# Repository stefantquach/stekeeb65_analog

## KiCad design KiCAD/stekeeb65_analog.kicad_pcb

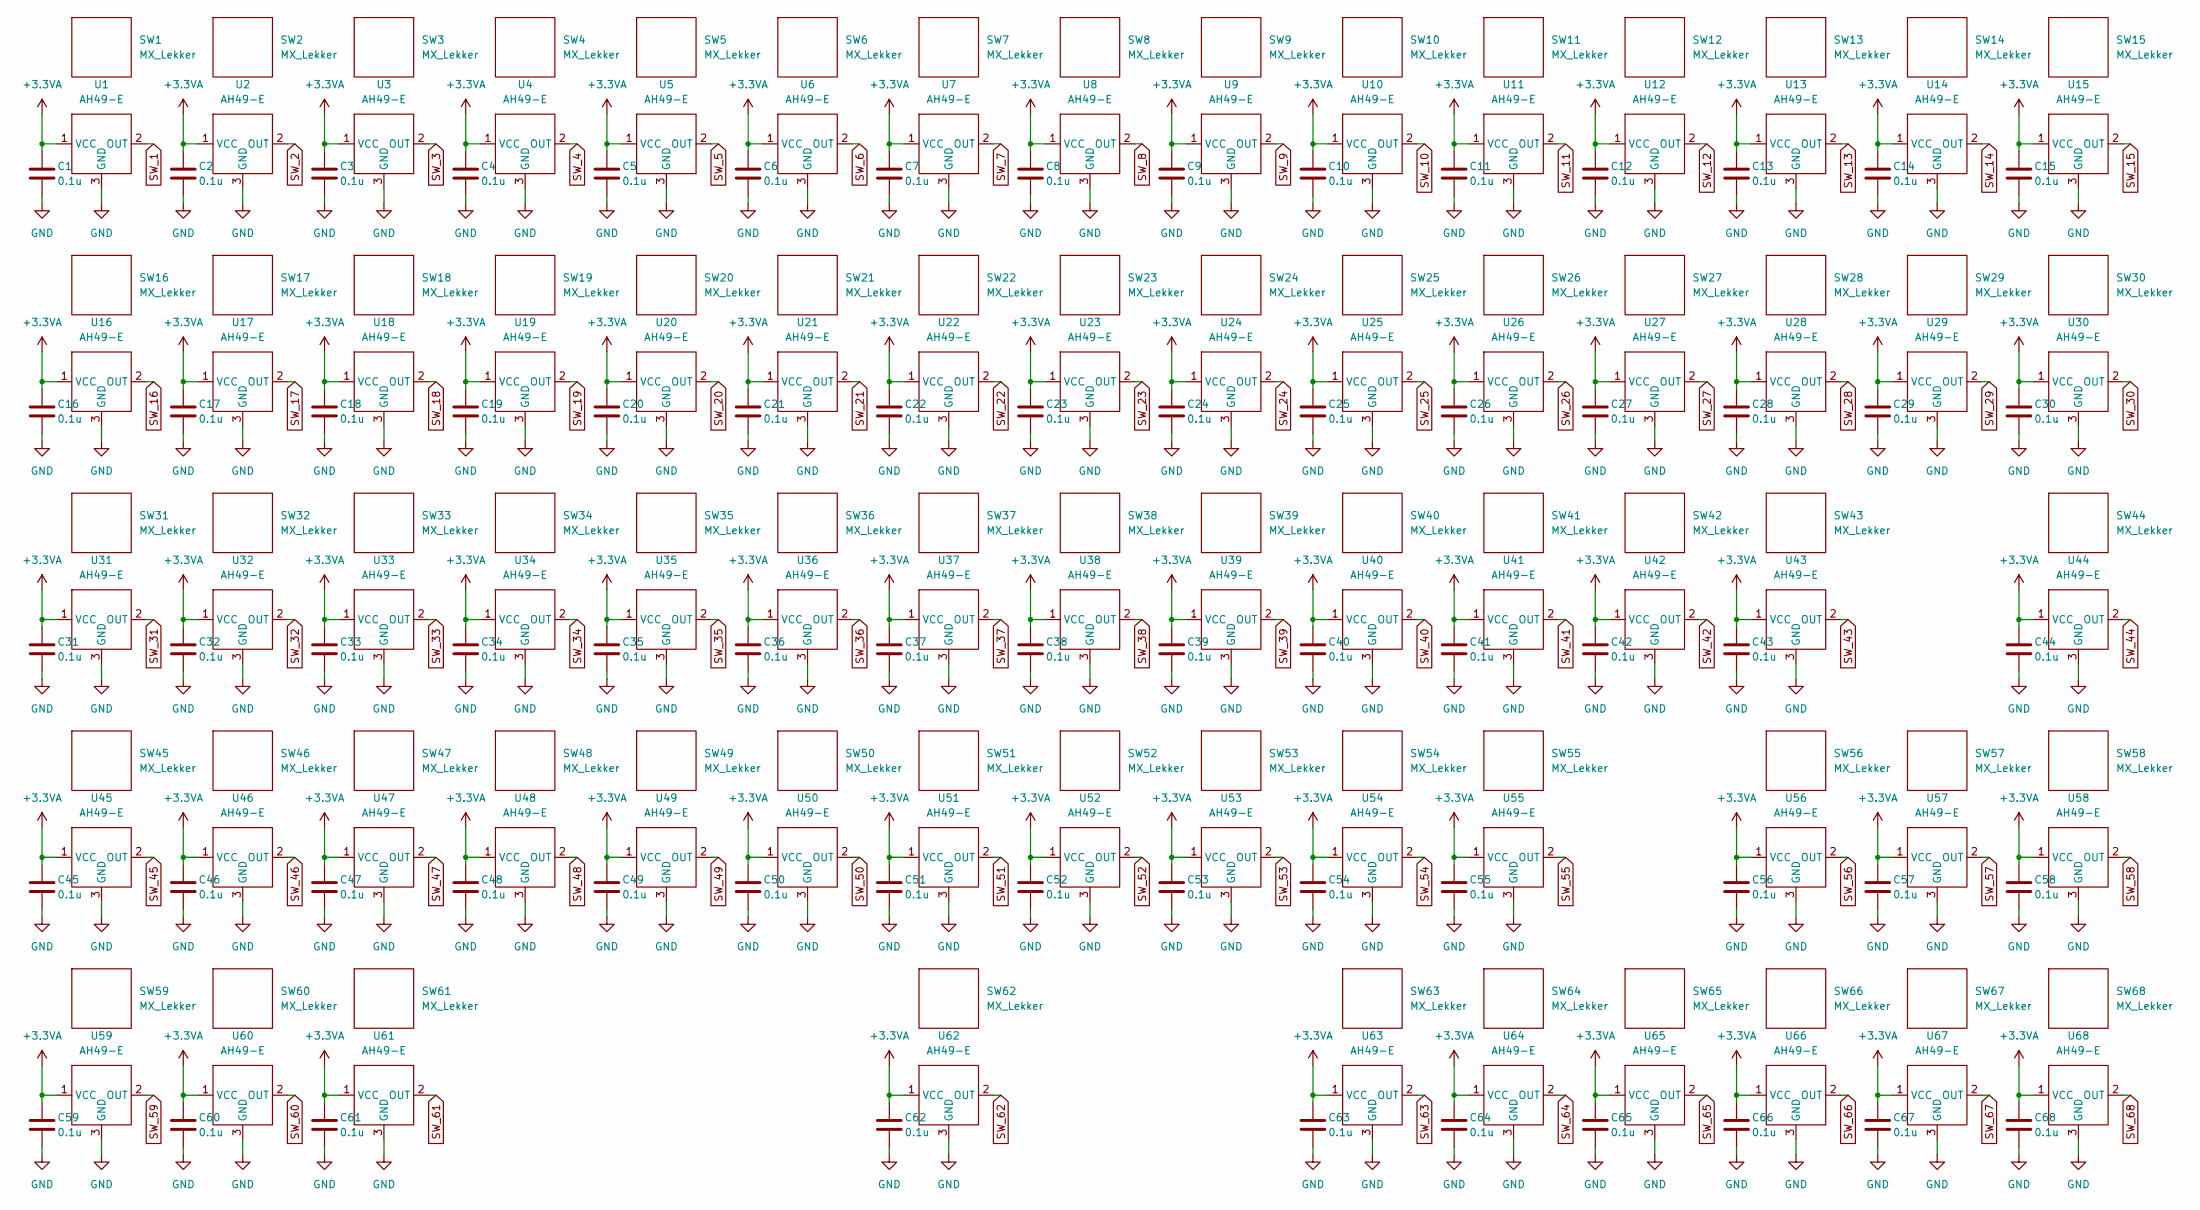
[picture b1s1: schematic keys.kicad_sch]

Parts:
C1, C2, C3, C4, C5, C6, C7, C8, C9, C10, C11, C12, C13, C14, C15, C16, C17, C18, C19, C20, C21, C22, C23, C24, C25, C26, C27, C28, C29, C30, C31, C32, C33, C34, C35, C36, C37, C38, C39, C40, C41, C42, C43, C44, C45, C46, C47, C48, C49, C50, C51, C52, C53, C54, C55, C56, C57, C58, C59, C60, C61, C62, C63, C64, C65, C66, C67, C68: 0.1u; C_0603_1608Metric_Pad1.08x0.95mm_HandSolder; Part Number C0603C104M4RAC7411
SW1, SW2, SW3, SW4, SW5, SW6, SW7, SW8, SW9, SW10, SW11, SW12, SW13, SW15, SW17, SW18, SW19, SW20, SW21, SW22, SW23, SW24, SW25, SW26, SW27, SW28, SW30, SW32, SW33, SW34, SW35, SW36, SW37, SW38, SW39, SW40, SW41, SW42, SW44, SW46, SW47, SW48, SW49, SW50, SW51, SW52, SW53, SW54, SW55, SW57, SW58, SW63, SW64, SW65, SW66, SW67, SW68: MX_Lekker
SW14: MX_Lekker; MX_Lekker-2U
SW16, SW29: MX_Lekker; MX_Lekker-1.5U
SW31, SW56: MX_Lekker; MX_Lekker-1.75U
SW43, SW45: MX_Lekker; MX_Lekker-2.25U
SW59, SW60, SW61: MX_Lekker; MX_Lekker-1.25U
SW62: MX_Lekker; MX_Lekker-6.25U-ReversedStabilizers
U1, U2, U3, U4, U5, U6, U7, U8, U9, U10, U11, U12, U13, U14, U15, U16, U17, U18, U19, U20, U21, U22, U23, U24, U25, U26, U27, U28, U29, U30, U31, U32, U33, U34, U35, U36, U37, U38, U39, U40, U41, U42, U43, U44, U45, U46, U47, U48, U49, U50, U51, U52, U53, U54, U55, U56, U57, U58, U59, U60, U61, U62, U63, U64, U65, U66, U67, U68: AH49-E; SOT-23_Handsoldering_no_plane

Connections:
+3.3VA: C1.1, C2.1, C3.1, C4.1, C5.1, C6.1, C7.1, C8.1, C9.1, C10.1, C11.1, C12.1, C13.1, C14.1, C15.1, C16.1, C17.1, C18.1, C19.1, C20.1, C21.1, C22.1, C23.1, C24.1, C25.1, C26.1, C27.1, C28.1, C29.1, C30.1, C31.1, C32.1, C33.1, C34.1, C35.1, C36.1, C37.1, C38.1, C39.1, C40.1, C41.1, C42.1, C43.1, C44.1, C45.1, C46.1, C47.1, C48.1, C49.1, C50.1, C51.1, C52.1, C53.1, C54.1, C55.1, C56.1, C57.1, C58.1, C59.1, C60.1, C61.1, C62.1, C63.1, C64.1, C65.1, C66.1, C67.1, C68.1, U1.1 (VCC), U2.1 (VCC), U3.1 (VCC), U4.1 (VCC), U5.1 (VCC), U6.1 (VCC), U7.1 (VCC), U8.1 (VCC), U9.1 (VCC), U10.1 (VCC), U11.1 (VCC), U12.1 (VCC), U13.1 (VCC), U14.1 (VCC), U15.1 (VCC), U16.1 (VCC), U17.1 (VCC), U18.1 (VCC), U19.1 (VCC), U20.1 (VCC), U21.1 (VCC), U22.1 (VCC), U23.1 (VCC), U24.1 (VCC), U25.1 (VCC), U26.1 (VCC), U27.1 (VCC), U28.1 (VCC), U29.1 (VCC), U30.1 (VCC), U31.1 (VCC), U32.1 (VCC), U33.1 (VCC), U34.1 (VCC), U35.1 (VCC), U36.1 (VCC), U37.1 (VCC), U38.1 (VCC), U39.1 (VCC), U40.1 (VCC), U41.1 (VCC), U42.1 (VCC), U43.1 (VCC), U44.1 (VCC), U45.1 (VCC), U46.1 (VCC), U47.1 (VCC), U48.1 (VCC), U49.1 (VCC), U50.1 (VCC), U51.1 (VCC), U52.1 (VCC), U53.1 (VCC), U54.1 (VCC), U55.1 (VCC), U56.1 (VCC), U57.1 (VCC), U58.1 (VCC), U59.1 (VCC), U60.1 (VCC), U61.1 (VCC), U62.1 (VCC), U63.1 (VCC), U64.1 (VCC), U65.1 (VCC), U66.1 (VCC), U67.1 (VCC), U68.1 (VCC); also elsewhere on the board
GND: C1.2, C2.2, C3.2, C4.2, C5.2, C6.2, C7.2, C8.2, C9.2, C10.2, C11.2, C12.2, C13.2, C14.2, C15.2, C16.2, C17.2, C18.2, C19.2, C20.2, C21.2, C22.2, C23.2, C24.2, C25.2, C26.2, C27.2, C28.2, C29.2, C30.2, C31.2, C32.2, C33.2, C34.2, C35.2, C36.2, C37.2, C38.2, C39.2, C40.2, C41.2, C42.2, C43.2, C44.2, C45.2, C46.2, C47.2, C48.2, C49.2, C50.2, C51.2, C52.2, C53.2, C54.2, C55.2, C56.2, C57.2, C58.2, C59.2, C60.2, C61.2, C62.2, C63.2, C64.2, C65.2, C66.2, C67.2, C68.2, U1.3 (GND), U2.3 (GND), U3.3 (GND), U4.3 (GND), U5.3 (GND), U6.3 (GND), U7.3 (GND), U8.3 (GND), U9.3 (GND), U10.3 (GND), U11.3 (GND), U12.3 (GND), U13.3 (GND), U14.3 (GND), U15.3 (GND), U16.3 (GND), U17.3 (GND), U18.3 (GND), U19.3 (GND), U20.3 (GND), U21.3 (GND), U22.3 (GND), U23.3 (GND), U24.3 (GND), U25.3 (GND), U26.3 (GND), U27.3 (GND), U28.3 (GND), U29.3 (GND), U30.3 (GND), U31.3 (GND), U32.3 (GND), U33.3 (GND), U34.3 (GND), U35.3 (GND), U36.3 (GND), U37.3 (GND), U38.3 (GND), U39.3 (GND), U40.3 (GND), U41.3 (GND), U42.3 (GND), U43.3 (GND), U44.3 (GND), U45.3 (GND), U46.3 (GND), U47.3 (GND), U48.3 (GND), U49.3 (GND), U50.3 (GND), U51.3 (GND), U52.3 (GND), U53.3 (GND), U54.3 (GND), U55.3 (GND), U56.3 (GND), U57.3 (GND), U58.3 (GND), U59.3 (GND), U60.3 (GND), U61.3 (GND), U62.3 (GND), U63.3 (GND), U64.3 (GND), U65.3 (GND), U66.3 (GND), U67.3 (GND), U68.3 (GND); also elsewhere on the board
SW_1: U1.2 (OUT); also elsewhere on the board
SW_2: U2.2 (OUT); also elsewhere on the board
SW_3: U3.2 (OUT); also elsewhere on the board
SW_4: U4.2 (OUT); also elsewhere on the board
SW_5: U5.2 (OUT); also elsewhere on the board
SW_6: U6.2 (OUT); also elsewhere on the board
SW_7: U7.2 (OUT); also elsewhere on the board
SW_8: U8.2 (OUT); also elsewhere on the board
SW_9: U9.2 (OUT); also elsewhere on the board
SW_10: U10.2 (OUT); also elsewhere on the board
SW_11: U11.2 (OUT); also elsewhere on the board
SW_12: U12.2 (OUT); also elsewhere on the board
SW_13: U13.2 (OUT); also elsewhere on the board
SW_14: U14.2 (OUT); also elsewhere on the board
SW_15: U15.2 (OUT)
SW_16: U16.2 (OUT); also elsewhere on the board
SW_17: U17.2 (OUT); also elsewhere on the board
SW_18: U18.2 (OUT); also elsewhere on the board
SW_19: U19.2 (OUT); also elsewhere on the board
SW_20: U20.2 (OUT); also elsewhere on the board
SW_21: U21.2 (OUT); also elsewhere on the board
SW_22: U22.2 (OUT); also elsewhere on the board
SW_23: U23.2 (OUT); also elsewhere on the board
SW_24: U24.2 (OUT); also elsewhere on the board
SW_25: U25.2 (OUT); also elsewhere on the board
SW_26: U26.2 (OUT); also elsewhere on the board
SW_27: U27.2 (OUT); also elsewhere on the board
SW_28: U28.2 (OUT); also elsewhere on the board
SW_29: U29.2 (OUT); also elsewhere on the board
SW_30: U30.2 (OUT)
SW_31: U31.2 (OUT); also elsewhere on the board
SW_32: U32.2 (OUT); also elsewhere on the board
SW_33: U33.2 (OUT); also elsewhere on the board
SW_34: U34.2 (OUT); also elsewhere on the board
SW_35: U35.2 (OUT); also elsewhere on the board
SW_36: U36.2 (OUT); also elsewhere on the board
SW_37: U37.2 (OUT); also elsewhere on the board
SW_38: U38.2 (OUT); also elsewhere on the board
SW_39: U39.2 (OUT)
SW_40: U40.2 (OUT)
SW_41: U41.2 (OUT)
SW_42: U42.2 (OUT)
SW_43: U43.2 (OUT)
SW_44: U44.2 (OUT)
SW_45: U45.2 (OUT); also elsewhere on the board
SW_46: U46.2 (OUT); also elsewhere on the board
SW_47: U47.2 (OUT); also elsewhere on the board
SW_48: U48.2 (OUT); also elsewhere on the board
SW_49: U49.2 (OUT); also elsewhere on the board
SW_50: U50.2 (OUT); also elsewhere on the board
SW_51: U51.2 (OUT); also elsewhere on the board
SW_52: U52.2 (OUT); also elsewhere on the board
SW_53: U53.2 (OUT)
SW_54: U54.2 (OUT)
SW_55: U55.2 (OUT)
SW_56: U56.2 (OUT)
SW_57: U57.2 (OUT)
SW_58: U58.2 (OUT)
SW_59: U59.2 (OUT); also elsewhere on the board
SW_60: U60.2 (OUT); also elsewhere on the board
SW_61: U61.2 (OUT); also elsewhere on the board
SW_62: U62.2 (OUT); also elsewhere on the board
SW_63: U63.2 (OUT)
SW_64: U64.2 (OUT)
SW_65: U65.2 (OUT)
SW_66: U66.2 (OUT)
SW_67: U67.2 (OUT)
SW_68: U68.2 (OUT)

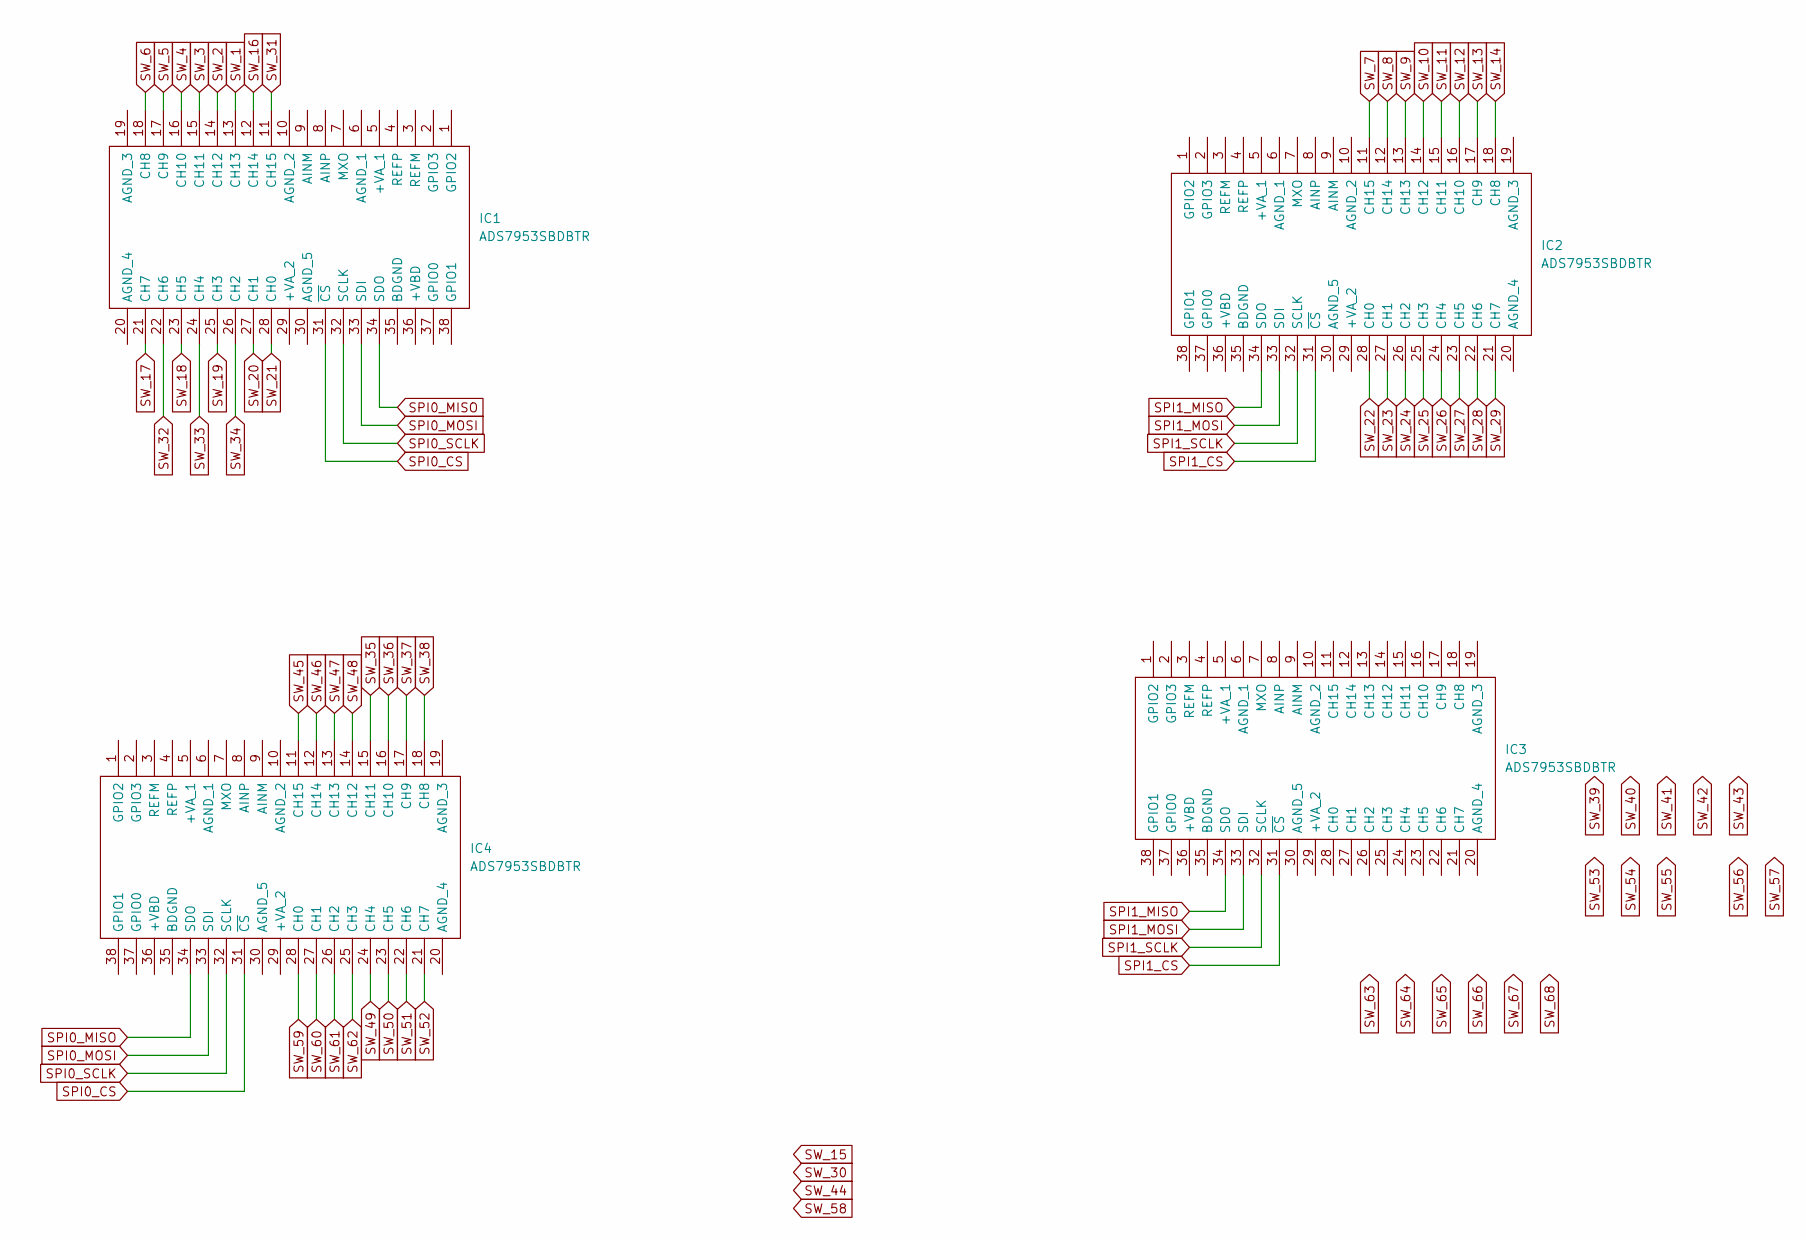
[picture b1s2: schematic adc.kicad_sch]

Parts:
IC1, IC2, IC3, IC4: ADS7953SBDBTR; TSSOP-38_4.4x9.7mm_P0.5mm; Manufacturer_Part_Number ADS7953SBDBTR; Mouser Part Number 595-ADS7953BDBTR

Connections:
SPI0_CS: IC1.31 (~CS), IC4.31 (~CS); also elsewhere on the board
SPI0_MISO: IC1.34 (SDO), IC4.34 (SDO); also elsewhere on the board
SPI0_MOSI: IC1.33 (SDI), IC4.33 (SDI); also elsewhere on the board
SPI0_SCLK: IC1.32 (SCLK), IC4.32 (SCLK); also elsewhere on the board
SPI1_CS: IC2.31 (~CS), IC3.31 (~CS); also elsewhere on the board
SPI1_MISO: IC2.34 (SDO), IC3.34 (SDO); also elsewhere on the board
SPI1_MOSI: IC2.33 (SDI), IC3.33 (SDI); also elsewhere on the board
SPI1_SCLK: IC2.32 (SCLK), IC3.32 (SCLK); also elsewhere on the board
SW_1: IC1.13 (CH13); also elsewhere on the board
SW_2: IC1.14 (CH12); also elsewhere on the board
SW_3: IC1.15 (CH11); also elsewhere on the board
SW_4: IC1.16 (CH10); also elsewhere on the board
SW_5: IC1.17 (CH9); also elsewhere on the board
SW_6: IC1.18 (CH8); also elsewhere on the board
SW_7: IC2.11 (CH15); also elsewhere on the board
SW_8: IC2.12 (CH14); also elsewhere on the board
SW_9: IC2.13 (CH13); also elsewhere on the board
SW_10: IC2.14 (CH12); also elsewhere on the board
SW_11: IC2.15 (CH11); also elsewhere on the board
SW_12: IC2.16 (CH10); also elsewhere on the board
SW_13: IC2.17 (CH9); also elsewhere on the board
SW_14: IC2.18 (CH8); also elsewhere on the board
SW_16: IC1.12 (CH14); also elsewhere on the board
SW_17: IC1.21 (CH7); also elsewhere on the board
SW_18: IC1.23 (CH5); also elsewhere on the board
SW_19: IC1.25 (CH3); also elsewhere on the board
SW_20: IC1.27 (CH1); also elsewhere on the board
SW_21: IC1.28 (CH0); also elsewhere on the board
SW_22: IC2.28 (CH0); also elsewhere on the board
SW_23: IC2.27 (CH1); also elsewhere on the board
SW_24: IC2.26 (CH2); also elsewhere on the board
SW_25: IC2.25 (CH3); also elsewhere on the board
SW_26: IC2.24 (CH4); also elsewhere on the board
SW_27: IC2.23 (CH5); also elsewhere on the board
SW_28: IC2.22 (CH6); also elsewhere on the board
SW_29: IC2.21 (CH7); also elsewhere on the board
SW_31: IC1.11 (CH15); also elsewhere on the board
SW_32: IC1.22 (CH6); also elsewhere on the board
SW_33: IC1.24 (CH4); also elsewhere on the board
SW_34: IC1.26 (CH2); also elsewhere on the board
SW_35: IC4.15 (CH11); also elsewhere on the board
SW_36: IC4.16 (CH10); also elsewhere on the board
SW_37: IC4.17 (CH9); also elsewhere on the board
SW_38: IC4.18 (CH8); also elsewhere on the board
SW_45: IC4.11 (CH15); also elsewhere on the board
SW_46: IC4.12 (CH14); also elsewhere on the board
SW_47: IC4.13 (CH13); also elsewhere on the board
SW_48: IC4.14 (CH12); also elsewhere on the board
SW_49: IC4.24 (CH4); also elsewhere on the board
SW_50: IC4.23 (CH5); also elsewhere on the board
SW_51: IC4.22 (CH6); also elsewhere on the board
SW_52: IC4.21 (CH7); also elsewhere on the board
SW_59: IC4.28 (CH0); also elsewhere on the board
SW_60: IC4.27 (CH1); also elsewhere on the board
SW_61: IC4.26 (CH2); also elsewhere on the board
SW_62: IC4.25 (CH3); also elsewhere on the board

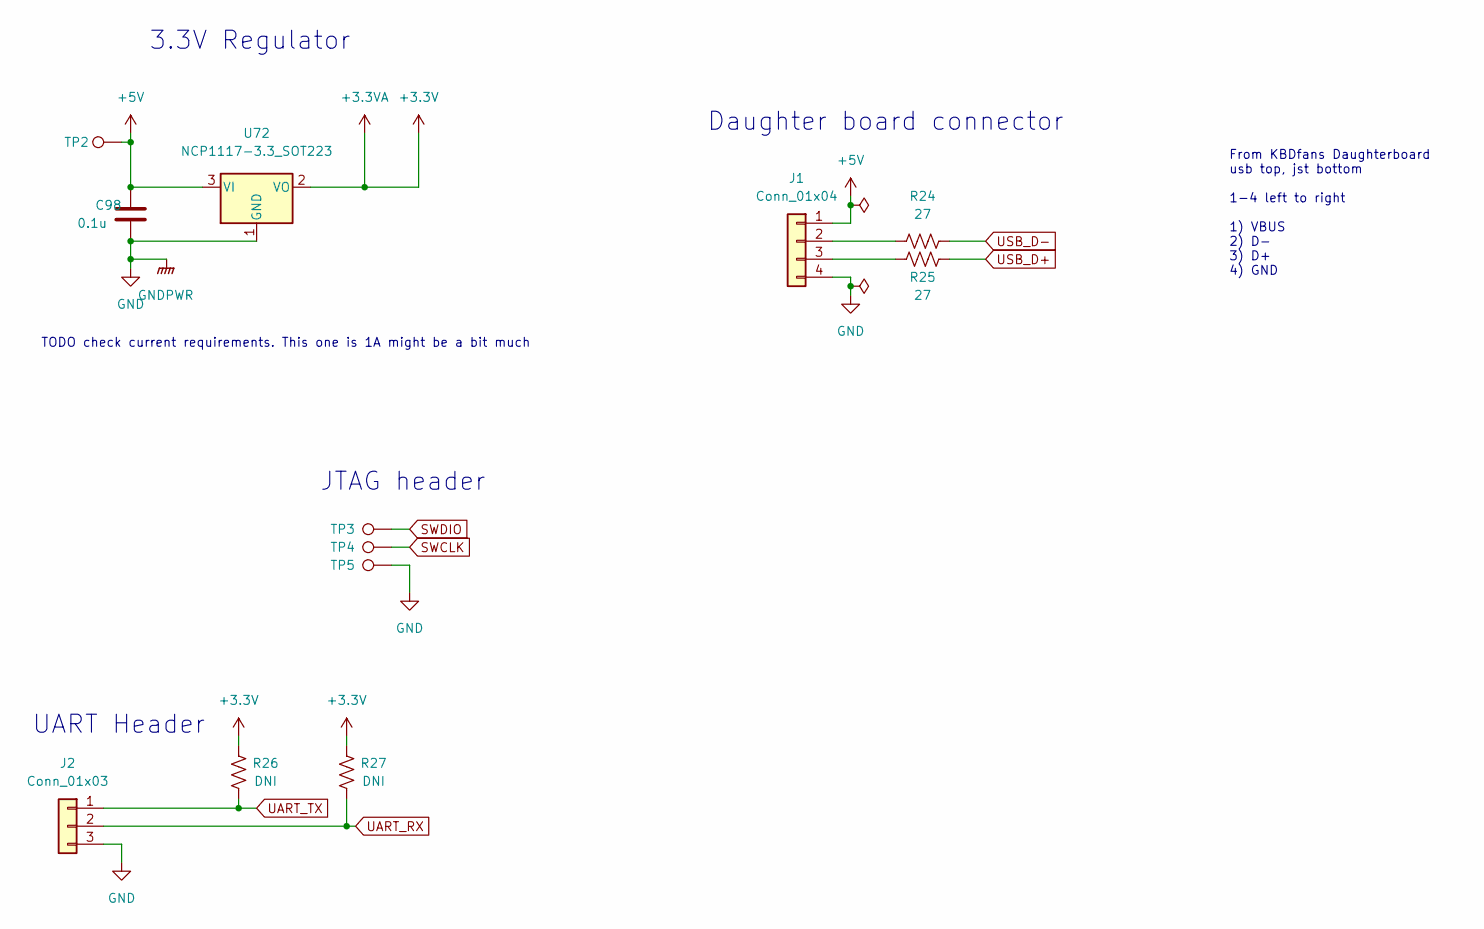
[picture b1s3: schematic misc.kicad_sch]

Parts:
C98: 0.1u; C_0603_1608Metric_Pad1.08x0.95mm_HandSolder; Part Number C0603C104M4RAC7411
J1: Conn_01x04; JST_SH_SM04B-SRSS-TB_1x04-1MP_P1.00mm_Horizontal
J2: Conn_01x03; PinHeader_1x03_P2.54mm_Vertical
R24, R25: 27; R_0603_1608Metric_Pad0.98x0.95mm_HandSolder
R26, R27: DNI; R_0603_1608Metric_Pad0.98x0.95mm_HandSolder
TP2, TP3, TP4, TP5: TestPoint; TestPoint_Pad_1.5x1.5mm
U72: NCP1117-3.3_SOT223; SOT-223-3_TabPin2; Part Number AZ1117IH-3.3TRG1

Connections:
+3.3VA: R26.1, R27.1, U72.2 (VO); also elsewhere on the board
+5V: C98.2, J1.1, TP2.1, U72.3 (VI)
GND: C98.1, J1.4, J2.3, TP5.1, U72.1 (GND); also elsewhere on the board
unnamed: J1.2, R24.1
unnamed: J1.3, R25.2
SWCLK: TP4.1; also elsewhere on the board
SWDIO: TP3.1; also elsewhere on the board
UART_RX: J2.2, R27.2; also elsewhere on the board
UART_TX: J2.1, R26.2; also elsewhere on the board
USB_D+: R25.1; also elsewhere on the board
USB_D-: R24.2; also elsewhere on the board

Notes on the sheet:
3.3V Regulator
JTAG header
UART Header
From KBDfans Daughterboard usb top, jst bottom 1-4 left to right 1) VBUS 2) D- 3) D+ 4) GND
Daughter board connector
TODO check current requirements. This one is 1A might be a bit much

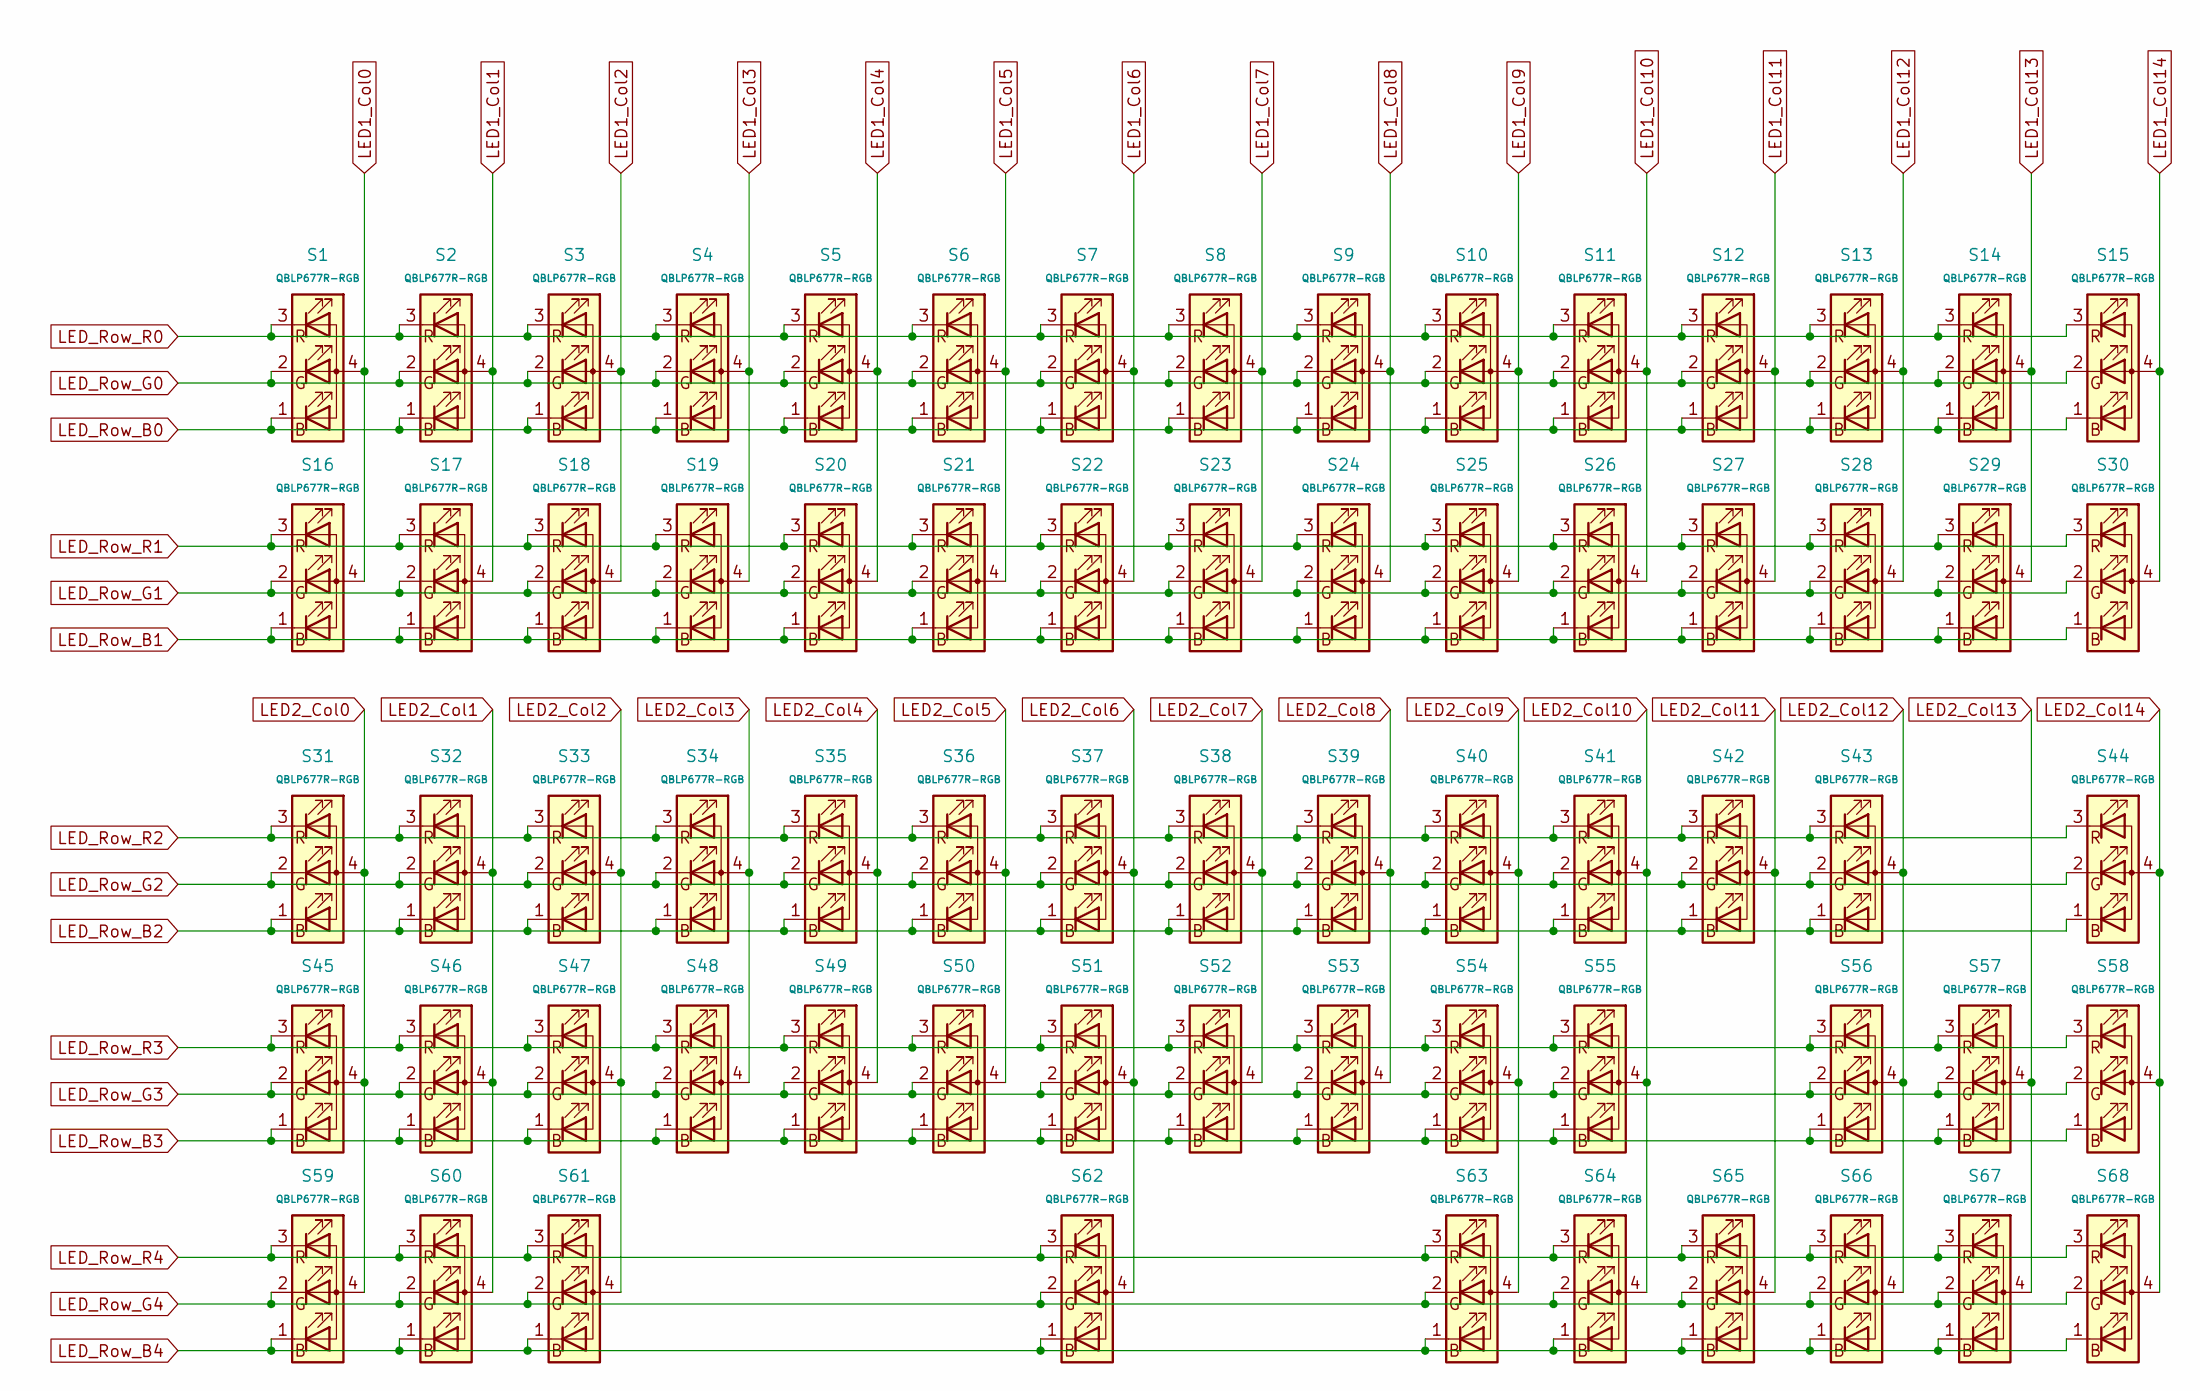
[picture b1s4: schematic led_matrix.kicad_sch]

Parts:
S1, S2, S3, S4, S5, S6, S7, S8, S9, S10, S11, S12, S13, S14, S15, S16, S17, S18, S19, S20, S21, S22, S23, S24, S25, S26, S27, S28, S29, S30, S31, S32, S33, S34, S35, S36, S37, S38, S39, S40, S41, S42, S43, S44, S45, S46, S47, S48, S49, S50, S51, S52, S53, S54, S55, S56, S57, S58, S59, S60, S61, S62, S63, S64, S65, S66, S67, S68: QBLP677R-RGB; QBLP677R-RGB-square_cutout

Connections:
LED1_Col0: S1.4 (A), S16.4 (A); also elsewhere on the board
LED1_Col1: S2.4 (A), S17.4 (A); also elsewhere on the board
LED1_Col2: S3.4 (A), S18.4 (A); also elsewhere on the board
LED1_Col3: S4.4 (A), S19.4 (A); also elsewhere on the board
LED1_Col4: S5.4 (A), S20.4 (A); also elsewhere on the board
LED1_Col5: S6.4 (A), S21.4 (A); also elsewhere on the board
LED1_Col6: S7.4 (A), S22.4 (A); also elsewhere on the board
LED1_Col7: S8.4 (A), S23.4 (A); also elsewhere on the board
LED1_Col8: S9.4 (A), S24.4 (A); also elsewhere on the board
LED1_Col9: S10.4 (A), S25.4 (A); also elsewhere on the board
LED1_Col10: S11.4 (A), S26.4 (A); also elsewhere on the board
LED1_Col11: S12.4 (A), S27.4 (A); also elsewhere on the board
LED1_Col12: S13.4 (A), S28.4 (A); also elsewhere on the board
LED1_Col13: S14.4 (A), S29.4 (A); also elsewhere on the board
LED1_Col14: S15.4 (A), S30.4 (A); also elsewhere on the board
LED2_Col0: S31.4 (A), S45.4 (A), S59.4 (A); also elsewhere on the board
LED2_Col1: S32.4 (A), S46.4 (A), S60.4 (A); also elsewhere on the board
LED2_Col2: S33.4 (A), S47.4 (A), S61.4 (A); also elsewhere on the board
LED2_Col3: S34.4 (A), S48.4 (A); also elsewhere on the board
LED2_Col4: S35.4 (A), S49.4 (A); also elsewhere on the board
LED2_Col5: S36.4 (A), S50.4 (A); also elsewhere on the board
LED2_Col6: S37.4 (A), S51.4 (A), S62.4 (A); also elsewhere on the board
LED2_Col7: S38.4 (A), S52.4 (A); also elsewhere on the board
LED2_Col8: S39.4 (A), S53.4 (A); also elsewhere on the board
LED2_Col9: S40.4 (A), S54.4 (A), S63.4 (A); also elsewhere on the board
LED2_Col10: S41.4 (A), S55.4 (A), S64.4 (A); also elsewhere on the board
LED2_Col11: S42.4 (A), S65.4 (A); also elsewhere on the board
LED2_Col12: S43.4 (A), S56.4 (A), S66.4 (A); also elsewhere on the board
LED2_Col13: S57.4 (A), S67.4 (A); also elsewhere on the board
LED2_Col14: S44.4 (A), S58.4 (A), S68.4 (A); also elsewhere on the board
LED_Row_B0: S1.1 (BK), S2.1 (BK), S3.1 (BK), S4.1 (BK), S5.1 (BK), S6.1 (BK), S7.1 (BK), S8.1 (BK), S9.1 (BK), S10.1 (BK), S11.1 (BK), S12.1 (BK), S13.1 (BK), S14.1 (BK), S15.1 (BK); also elsewhere on the board
LED_Row_B1: S16.1 (BK), S17.1 (BK), S18.1 (BK), S19.1 (BK), S20.1 (BK), S21.1 (BK), S22.1 (BK), S23.1 (BK), S24.1 (BK), S25.1 (BK), S26.1 (BK), S27.1 (BK), S28.1 (BK), S29.1 (BK), S30.1 (BK); also elsewhere on the board
LED_Row_B2: S31.1 (BK), S32.1 (BK), S33.1 (BK), S34.1 (BK), S35.1 (BK), S36.1 (BK), S37.1 (BK), S38.1 (BK), S39.1 (BK), S40.1 (BK), S41.1 (BK), S42.1 (BK), S43.1 (BK), S44.1 (BK); also elsewhere on the board
LED_Row_B3: S45.1 (BK), S46.1 (BK), S47.1 (BK), S48.1 (BK), S49.1 (BK), S50.1 (BK), S51.1 (BK), S52.1 (BK), S53.1 (BK), S54.1 (BK), S55.1 (BK), S56.1 (BK), S57.1 (BK), S58.1 (BK); also elsewhere on the board
LED_Row_B4: S59.1 (BK), S60.1 (BK), S61.1 (BK), S62.1 (BK), S63.1 (BK), S64.1 (BK), S65.1 (BK), S66.1 (BK), S67.1 (BK), S68.1 (BK); also elsewhere on the board
LED_Row_G0: S1.2 (GK), S2.2 (GK), S3.2 (GK), S4.2 (GK), S5.2 (GK), S6.2 (GK), S7.2 (GK), S8.2 (GK), S9.2 (GK), S10.2 (GK), S11.2 (GK), S12.2 (GK), S13.2 (GK), S14.2 (GK), S15.2 (GK); also elsewhere on the board
LED_Row_G1: S16.2 (GK), S17.2 (GK), S18.2 (GK), S19.2 (GK), S20.2 (GK), S21.2 (GK), S22.2 (GK), S23.2 (GK), S24.2 (GK), S25.2 (GK), S26.2 (GK), S27.2 (GK), S28.2 (GK), S29.2 (GK), S30.2 (GK); also elsewhere on the board
LED_Row_G2: S31.2 (GK), S32.2 (GK), S33.2 (GK), S34.2 (GK), S35.2 (GK), S36.2 (GK), S37.2 (GK), S38.2 (GK), S39.2 (GK), S40.2 (GK), S41.2 (GK), S42.2 (GK), S43.2 (GK), S44.2 (GK); also elsewhere on the board
LED_Row_G3: S45.2 (GK), S46.2 (GK), S47.2 (GK), S48.2 (GK), S49.2 (GK), S50.2 (GK), S51.2 (GK), S52.2 (GK), S53.2 (GK), S54.2 (GK), S55.2 (GK), S56.2 (GK), S57.2 (GK), S58.2 (GK); also elsewhere on the board
LED_Row_G4: S59.2 (GK), S60.2 (GK), S61.2 (GK), S62.2 (GK), S63.2 (GK), S64.2 (GK), S65.2 (GK), S66.2 (GK), S67.2 (GK), S68.2 (GK); also elsewhere on the board
LED_Row_R0: S1.3 (RK), S2.3 (RK), S3.3 (RK), S4.3 (RK), S5.3 (RK), S6.3 (RK), S7.3 (RK), S8.3 (RK), S9.3 (RK), S10.3 (RK), S11.3 (RK), S12.3 (RK), S13.3 (RK), S14.3 (RK), S15.3 (RK); also elsewhere on the board
LED_Row_R1: S16.3 (RK), S17.3 (RK), S18.3 (RK), S19.3 (RK), S20.3 (RK), S21.3 (RK), S22.3 (RK), S23.3 (RK), S24.3 (RK), S25.3 (RK), S26.3 (RK), S27.3 (RK), S28.3 (RK), S29.3 (RK), S30.3 (RK); also elsewhere on the board
LED_Row_R2: S31.3 (RK), S32.3 (RK), S33.3 (RK), S34.3 (RK), S35.3 (RK), S36.3 (RK), S37.3 (RK), S38.3 (RK), S39.3 (RK), S40.3 (RK), S41.3 (RK), S42.3 (RK), S43.3 (RK), S44.3 (RK); also elsewhere on the board
LED_Row_R3: S45.3 (RK), S46.3 (RK), S47.3 (RK), S48.3 (RK), S49.3 (RK), S50.3 (RK), S51.3 (RK), S52.3 (RK), S53.3 (RK), S54.3 (RK), S55.3 (RK), S56.3 (RK), S57.3 (RK), S58.3 (RK); also elsewhere on the board
LED_Row_R4: S59.3 (RK), S60.3 (RK), S61.3 (RK), S62.3 (RK), S63.3 (RK), S64.3 (RK), S65.3 (RK), S66.3 (RK), S67.3 (RK), S68.3 (RK); also elsewhere on the board

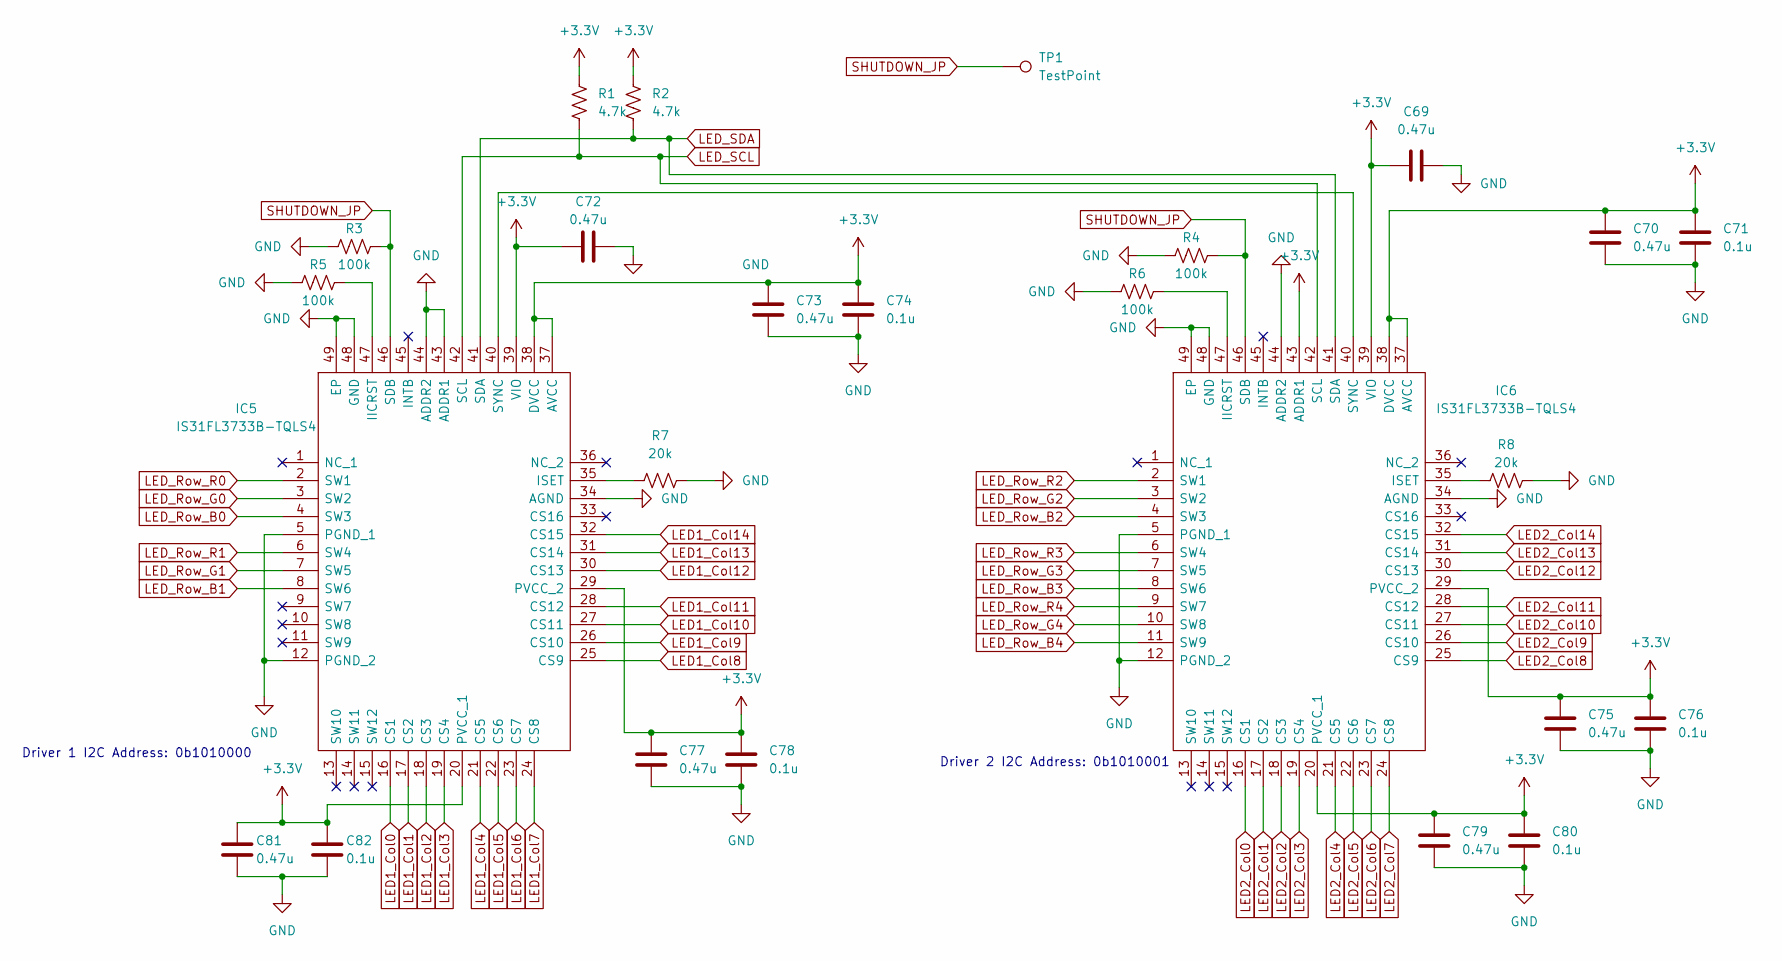
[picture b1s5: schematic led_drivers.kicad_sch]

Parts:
C69, C70, C72, C73, C75, C77, C79, C81: 0.47u; C_0603_1608Metric_Pad1.08x0.95mm_HandSolder
C71, C74, C76, C78, C80, C82: 0.1u; C_0603_1608Metric_Pad1.08x0.95mm_HandSolder; Part Number C0603C104M4RAC7411
IC5, IC6: IS31FL3733B-TQLS4; QFP50P900X900X120-49N; Manufacturer_Part_Number IS31FL3733B-TQLS4; Mouser Part Number 870-IS313733B-TQLS4
R1, R2: 4.7k; R_0603_1608Metric_Pad0.98x0.95mm_HandSolder
R3, R4, R5, R6: 100k; R_0603_1608Metric_Pad0.98x0.95mm_HandSolder
R7, R8: 20k; R_0603_1608Metric_Pad0.98x0.95mm_HandSolder
TP1: TestPoint; TestPoint_Pad_D1.0mm

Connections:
+3.3VA: C69.1, C70.1, C71.1, C72.1, C73.1, C74.1, C75.1, C76.1, C77.1, C78.1, C79.1, C80.1, C81.1, C82.1, IC5.20 (PVCC_1), IC5.29 (PVCC_2), IC5.37 (AVCC), IC5.38 (DVCC), IC5.39 (VIO), IC6.20 (PVCC_1), IC6.29 (PVCC_2), IC6.37 (AVCC), IC6.38 (DVCC), IC6.39 (VIO), IC6.43 (ADDR1), R1.1, R2.1; also elsewhere on the board
GND: C69.2, C70.2, C71.2, C72.2, C73.2, C74.2, C75.2, C76.2, C77.2, C78.2, C79.2, C80.2, C81.2, C82.2, IC5.5 (PGND_1), IC5.12 (PGND_2), IC5.34 (AGND), IC5.43 (ADDR1), IC5.44 (ADDR2), IC5.48 (GND), IC5.49 (EP), IC6.5 (PGND_1), IC6.12 (PGND_2), IC6.34 (AGND), IC6.44 (ADDR2), IC6.48 (GND), IC6.49 (EP), R3.1, R4.1, R5.1, R6.1, R7.2, R8.2; also elsewhere on the board
LED1_Col0: IC5.16 (CS1); also elsewhere on the board
LED1_Col1: IC5.17 (CS2); also elsewhere on the board
LED1_Col2: IC5.18 (CS3); also elsewhere on the board
LED1_Col3: IC5.19 (CS4); also elsewhere on the board
LED1_Col4: IC5.21 (CS5); also elsewhere on the board
LED1_Col5: IC5.22 (CS6); also elsewhere on the board
LED1_Col6: IC5.23 (CS7); also elsewhere on the board
LED1_Col7: IC5.24 (CS8); also elsewhere on the board
LED1_Col8: IC5.25 (CS9); also elsewhere on the board
LED1_Col9: IC5.26 (CS10); also elsewhere on the board
LED1_Col10: IC5.27 (CS11); also elsewhere on the board
LED1_Col11: IC5.28 (CS12); also elsewhere on the board
LED1_Col12: IC5.30 (CS13); also elsewhere on the board
LED1_Col13: IC5.31 (CS14); also elsewhere on the board
LED1_Col14: IC5.32 (CS15); also elsewhere on the board
LED2_Col0: IC6.16 (CS1); also elsewhere on the board
LED2_Col1: IC6.17 (CS2); also elsewhere on the board
LED2_Col2: IC6.18 (CS3); also elsewhere on the board
LED2_Col3: IC6.19 (CS4); also elsewhere on the board
LED2_Col4: IC6.21 (CS5); also elsewhere on the board
LED2_Col5: IC6.22 (CS6); also elsewhere on the board
LED2_Col6: IC6.23 (CS7); also elsewhere on the board
LED2_Col7: IC6.24 (CS8); also elsewhere on the board
LED2_Col8: IC6.25 (CS9); also elsewhere on the board
LED2_Col9: IC6.26 (CS10); also elsewhere on the board
LED2_Col10: IC6.27 (CS11); also elsewhere on the board
LED2_Col11: IC6.28 (CS12); also elsewhere on the board
LED2_Col12: IC6.30 (CS13); also elsewhere on the board
LED2_Col13: IC6.31 (CS14); also elsewhere on the board
LED2_Col14: IC6.32 (CS15); also elsewhere on the board
LED_Row_B0: IC5.4 (SW3); also elsewhere on the board
LED_Row_B1: IC5.8 (SW6); also elsewhere on the board
LED_Row_B2: IC6.4 (SW3); also elsewhere on the board
LED_Row_B3: IC6.8 (SW6); also elsewhere on the board
LED_Row_B4: IC6.11 (SW9); also elsewhere on the board
LED_Row_G0: IC5.3 (SW2); also elsewhere on the board
LED_Row_G1: IC5.7 (SW5); also elsewhere on the board
LED_Row_G2: IC6.3 (SW2); also elsewhere on the board
LED_Row_G3: IC6.7 (SW5); also elsewhere on the board
LED_Row_G4: IC6.10 (SW8); also elsewhere on the board
LED_Row_R0: IC5.2 (SW1); also elsewhere on the board
LED_Row_R1: IC5.6 (SW4); also elsewhere on the board
LED_Row_R2: IC6.2 (SW1); also elsewhere on the board
LED_Row_R3: IC6.6 (SW4); also elsewhere on the board
LED_Row_R4: IC6.9 (SW7); also elsewhere on the board
LED_SCL: IC5.42 (SCL), IC6.42 (SCL), R1.2; also elsewhere on the board
LED_SDA: IC5.41 (SDA), IC6.41 (SDA), R2.2; also elsewhere on the board
unnamed: IC5.35 (ISET), R7.1
unnamed: IC5.40 (SYNC), IC6.40 (SYNC)
unnamed: IC5.47 (IICRST), R5.2
unnamed: IC6.35 (ISET), R8.1
unnamed: IC6.47 (IICRST), R6.2
SHUTDOWN_JP: IC5.46 (SDB), IC6.46 (SDB), R3.2, R4.2, TP1.1

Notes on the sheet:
Driver 2 I2C Address: 0b1010001
Driver 1 I2C Address: 0b1010000
